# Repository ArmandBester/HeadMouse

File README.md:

# HeadMouse

### An Arduino based human interface device (HID)
This device uses an [Arduino Micro](https://store.arduino.cc/arduino-micro) and will probably work with any ATmega32U4 based development board.  A [gyroscope sensor](https://www.amazon.com/Gy-521-MPU-6050-MPU6050-Sensors-Accelerometer/dp/B008BOPN40) is used as input.  The gyroscope input is smoothed and scaled by the arduino and using the [Mouse library](https://www.arduino.cc/reference/en/language/functions/usb/mouse/) is able to emulate mouse movements on a computer screen.  A pressure sensor XGZP6847 is used as input for click and scroll control.  

* Short blow = left click
* Longer blow = scroll down
* Short suck = right click
* Longer suck = scroll up

When the device is powered on via a USB cable, it automatically calibrates the ambient pressure.

The HeadMouse can be mounted on a gaming headset, this allows a good scaffold for the electronics as well as the microphone extension to which a mouthpiece is fixed to enable convenient pressure control.

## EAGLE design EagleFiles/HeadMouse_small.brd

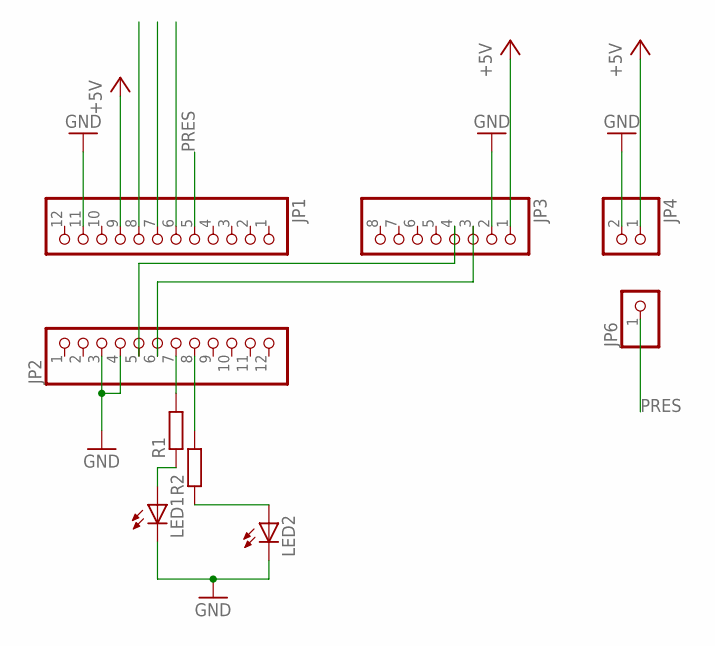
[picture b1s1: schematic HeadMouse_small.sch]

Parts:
JP1, JP2: PINHD-1X12; 1X12
JP3: PINHD-1X8BIG; 1X08-BIG
JP4: PINHD-1X2; 1X02
JP6: PINHD-1X1; 1X01
LED1, LED2: LED3MM
R1, R2: R-EU_0204/7; 0204/7

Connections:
+5V: JP1.9, JP3.1, JP4.1
GND: JP1.11, JP2.3, JP2.4, JP3.2, JP4.2, LED1.K (C), LED2.K (C)
unnamed: JP2.5, JP3.4
unnamed: JP2.8, R2.2
unnamed: LED1.A, R1.1
unnamed: LED2.A, R2.1
unnamed: JP2.7, R1.2
unnamed: JP2.6, JP3.3
PRES: JP1.5, JP6.1

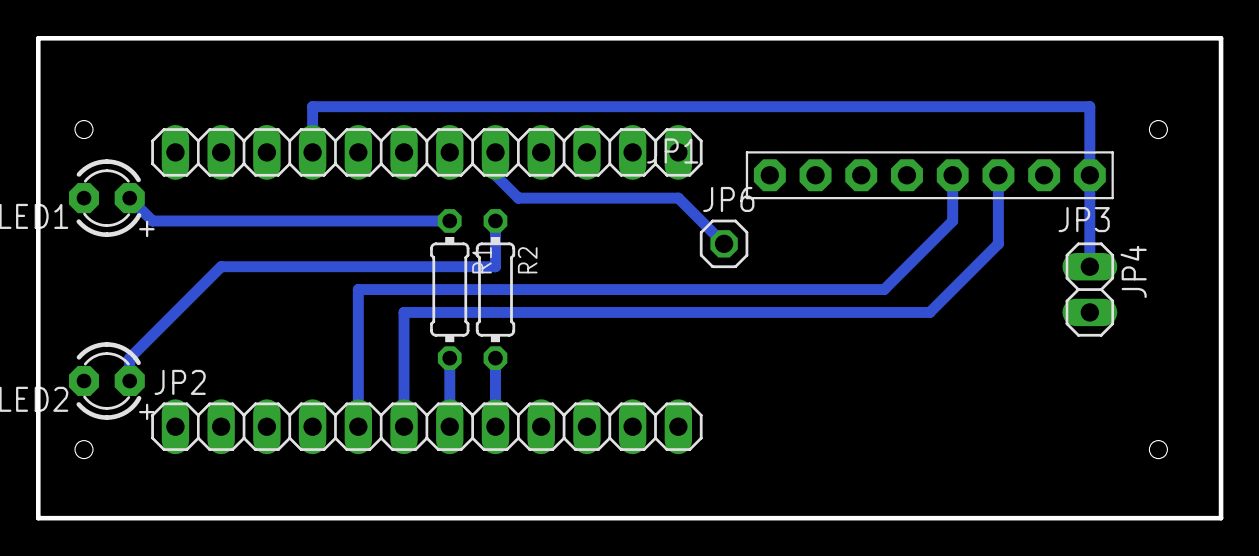
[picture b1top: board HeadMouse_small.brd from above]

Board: 2 copper layers, 65.7 x 26.7 mm, 9 parts (0 on the bottom side), 9 nets.

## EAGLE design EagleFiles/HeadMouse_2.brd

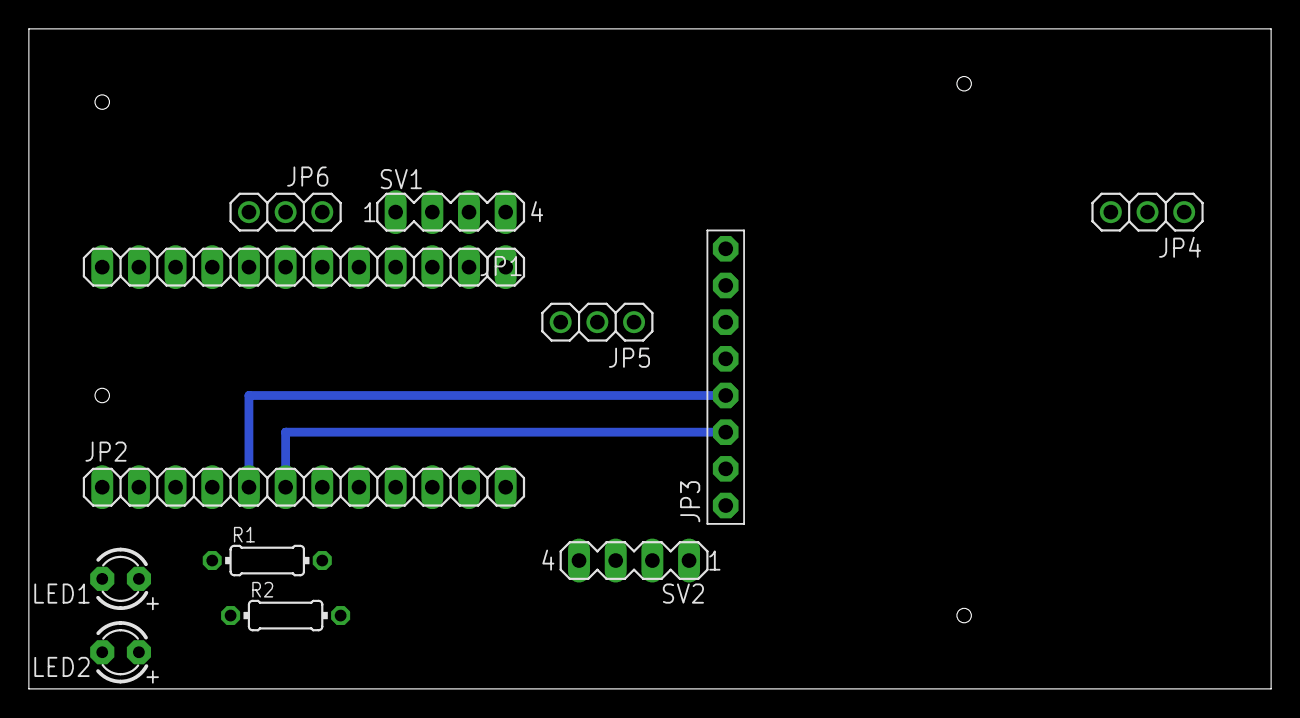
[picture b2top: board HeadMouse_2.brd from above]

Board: 2 copper layers, 86.0 x 45.7 mm, 12 parts (0 on the bottom side), 20 nets.

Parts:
JP1, JP2: 1X12
JP3: 1X08-BIG
JP4, JP5, JP6: 1X03
LED1, LED2: LED3MM
R1, R2: 0204/7
SV1, SV2: MA04-1

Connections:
+5V: JP1.9, JP3.1, JP4.2
GND: JP1.11, JP2.3, JP2.4, JP3.2, JP4.3, LED1.K, LED2.K
unnamed: JP2.5, JP3.4
unnamed: JP2.8, R2.2
unnamed: LED1.A, R1.1
unnamed: LED2.A, R2.1
unnamed: JP2.7, R1.2
unnamed: JP2.6, JP3.3
unnamed: JP1.8, JP6.1
unnamed: JP1.7, JP6.2
unnamed: JP1.6, JP6.3
unnamed: JP1.4, SV1.1
unnamed: JP1.3, SV1.2
unnamed: JP1.2, SV1.3
unnamed: JP1.1, SV1.4
unnamed: JP2.9, SV2.4
unnamed: JP2.10, SV2.3
unnamed: JP2.11, SV2.2
unnamed: JP2.12, SV2.1
PRES: JP1.5, JP5.2

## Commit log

2019-10-03 Added first bit of code
2019-10-03 Added some smoothing to mouse movement, this can be adjusted as needed
2019-10-03 Started with pressure sensor
2019-10-05 Added callibrations routine for ambient pressure
2019-10-05 Added positive and negative pressure timers
2019-10-06 Added clicking and scrolling
2019-10-06 Started with readme
2019-10-07 Added gerber and eagle cad files
2019-10-07 Fixed mistake in the Eagle folder
2019-10-07 Removed html readme
2019-10-21 Changes to averaging and pressure threshold.
